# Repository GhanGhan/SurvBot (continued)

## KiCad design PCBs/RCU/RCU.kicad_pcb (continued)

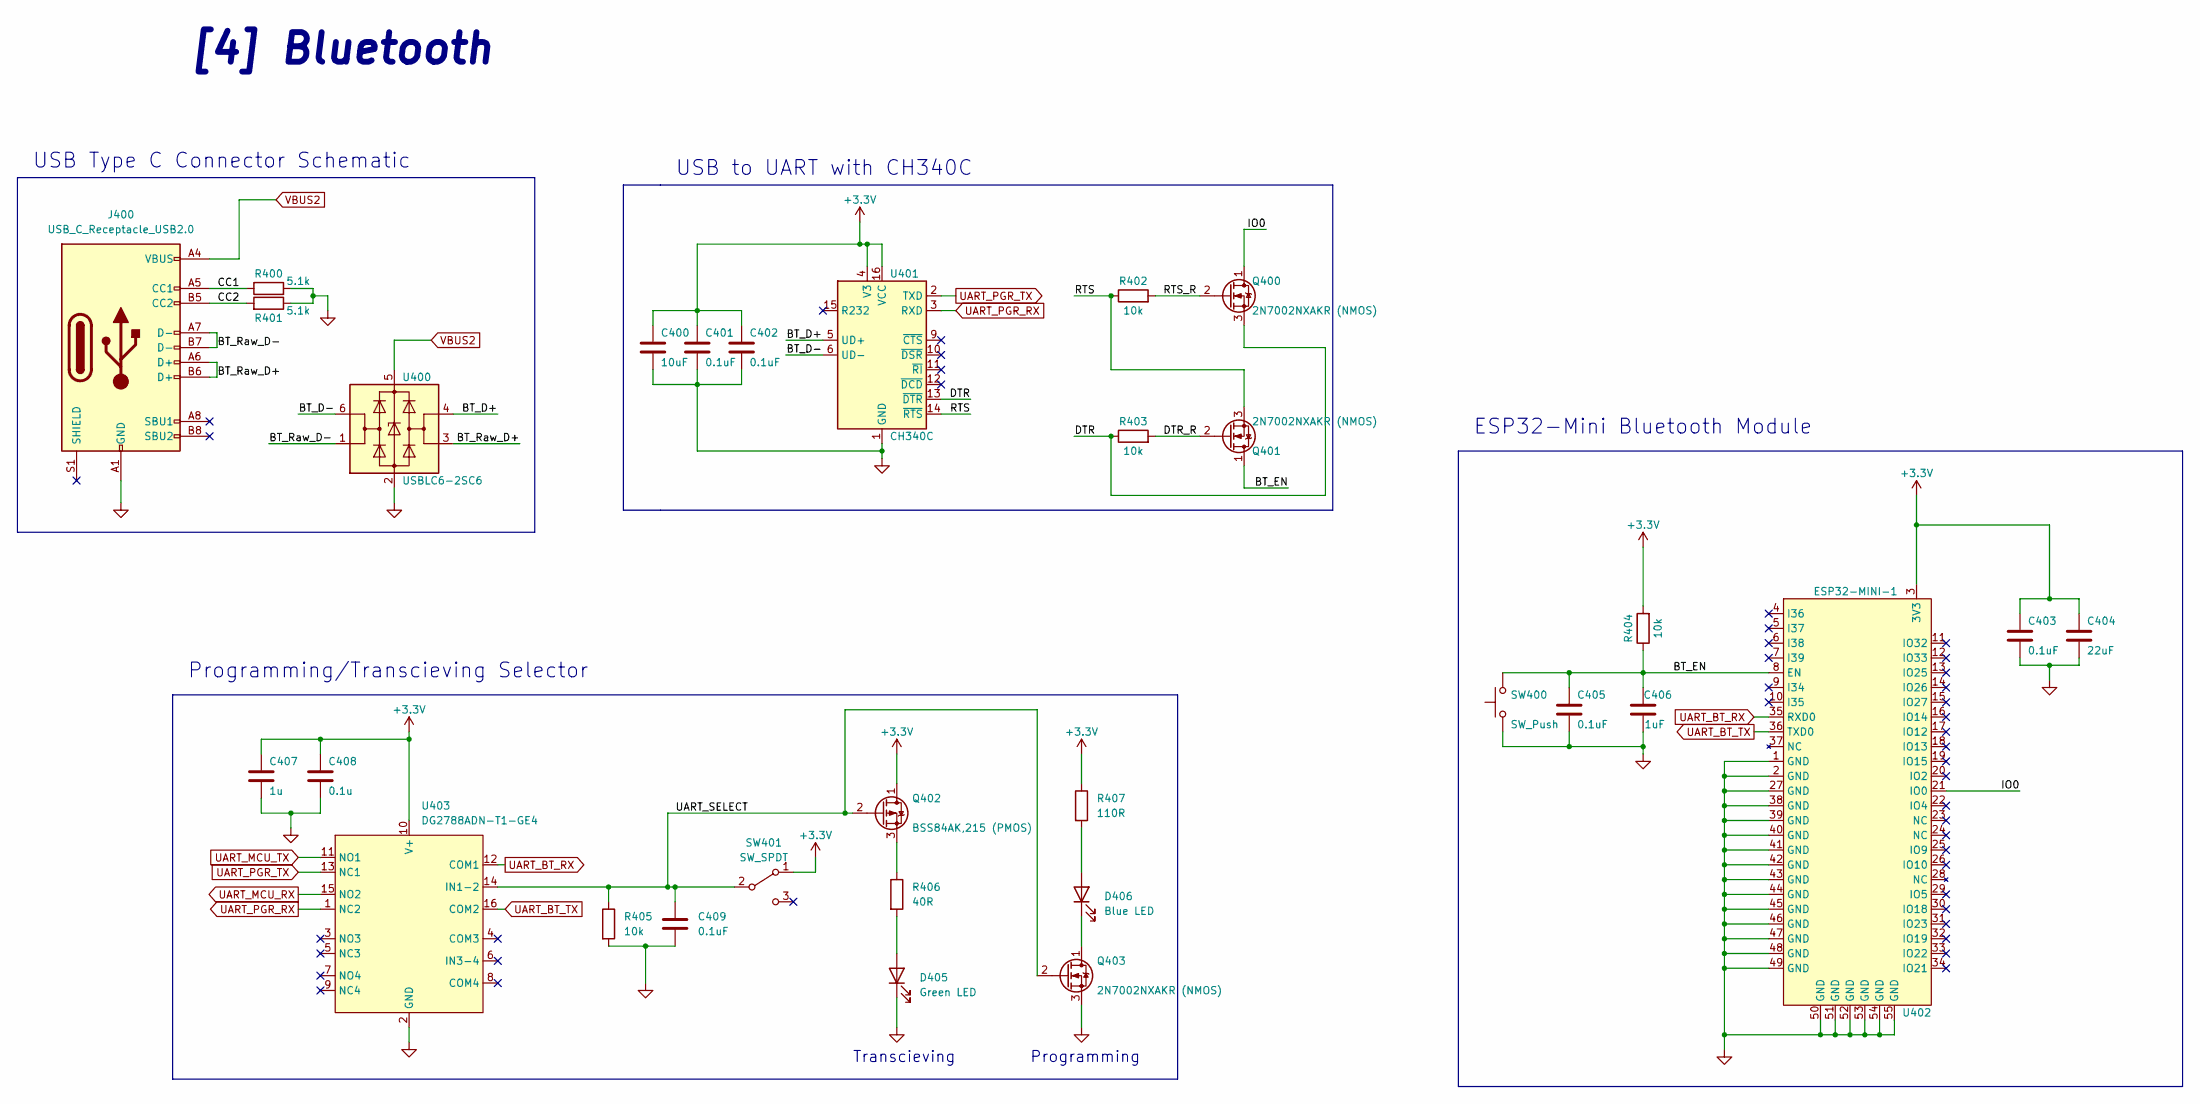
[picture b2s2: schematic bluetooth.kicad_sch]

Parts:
C400: 10uF; C_0603_1608Metric
C401, C402, C403, C405, C409: 0.1uF; C_0603_1608Metric
C404: 22uF; C_0603_1608Metric
C406: 1uF; C_0603_1608Metric
C407: 1u; C_0603_1608Metric
C408: 0.1u; C_0603_1608Metric
D405: Green LED; LED_0603_1608Metric
D406: Blue LED; LED_0603_1608Metric
J400: USB_C_Receptacle_USB2.0; USB_C_Receptacle_HRO_TYPE-C-31-M-12
Q400, Q401, Q403: 2N7002NXAKR (NMOS); SOT-23
Q402: BSS84AK,215 (PMOS); SOT-23
R400, R401: 5.1k; R_0603_1608Metric
R402, R403, R404, R405: 10k; R_0603_1608Metric
R406: 40R; R_0603_1608Metric
R407: 110R; R_0603_1608Metric
SW400: SW_Push; SW_SPST_B3U-1000P
SW401: SW_SPDT; SW_JS102011JCQN
U400: USBLC6-2SC6; SOT-23-6
U401: CH340C; SOP-16_3.9x9.9mm_P1.27mm
U402: ESP32-MINI-1; XCVR_ESP32-MINI-1-N4
U403: DG2788ADN-T1-GE4; QFN40P260X180X55-16N

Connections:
+3V3: C400.1, C401.1, C402.1, C403.1, C404.1, C407.1, C408.1, Q402.1 (D), R404.2, R407.1, SW401.1 (A), U401.4 (V3), U401.16 (VCC), U402.3 (3V3), U403.10 (V+); also elsewhere on the board
/[4] Bluetooth/BT_D+: U400.4 (I/O2), U401.5 (UD+)
/[4] Bluetooth/BT_D-: U400.6 (I/O1), U401.6 (UD-)
/[4] Bluetooth/BT_EN: C405.1, C406.1, Q401.1 (D), R404.1, SW400.2, U402.8 (EN)
/[4] Bluetooth/BT_Raw_D+: J400.A6 (D+), J400.B6 (D+), U400.3 (I/O2)
/[4] Bluetooth/BT_Raw_D-: J400.A7 (D-), J400.B7 (D-), U400.1 (I/O1)
/[4] Bluetooth/CC1: J400.A5 (CC1), R400.1
/[4] Bluetooth/CC2: J400.B5 (CC2), R401.2
/[4] Bluetooth/DTR: Q400.3 (S), R403.1, U401.13 (~DTR)
/[4] Bluetooth/DTR_R: Q401.2 (G), R403.2
/[4] Bluetooth/IO0: Q400.1 (D), U402.21 (IO0)
/[4] Bluetooth/RTS: Q401.3 (S), R402.1, U401.14 (~RTS)
/[4] Bluetooth/RTS_R: Q400.2 (G), R402.2
/[4] Bluetooth/UART_SELECT: C409.1, Q402.2 (G), Q403.2 (G), R405.1, SW401.2 (B), U403.14 (IN1-2)
unnamed: D405.2 (A), R406.2
unnamed: D406.1 (K), Q403.1 (D)
unnamed: D406.2 (A), R407.2
unnamed: Q402.3 (S), R406.1
UART_BT_RX: U402.35 (RXD0), U403.12 (COM1)
UART_BT_TX: U402.36 (TXD0), U403.16 (COM2)
UART_MCU_RX: U403.15 (NO2); also elsewhere on the board
UART_MCU_TX: U403.11 (NO1); also elsewhere on the board
UART_PGR_RX: U401.3 (RXD), U403.1 (NC2)
UART_PGR_TX: U401.2 (TXD), U403.13 (NC1)
VBUS2: J400.A4 (VBUS), J400.A9 (VBUS), J400.B4 (VBUS), J400.B9 (VBUS), U400.5 (VBUS); also elsewhere on the board

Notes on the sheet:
ESP32-Mini Bluetooth Module
[4] Bluetooth
Programming
USB Type C Connector Schematic
USB to UART with CH340C
Programming/Transcieving Selector
Transcieving

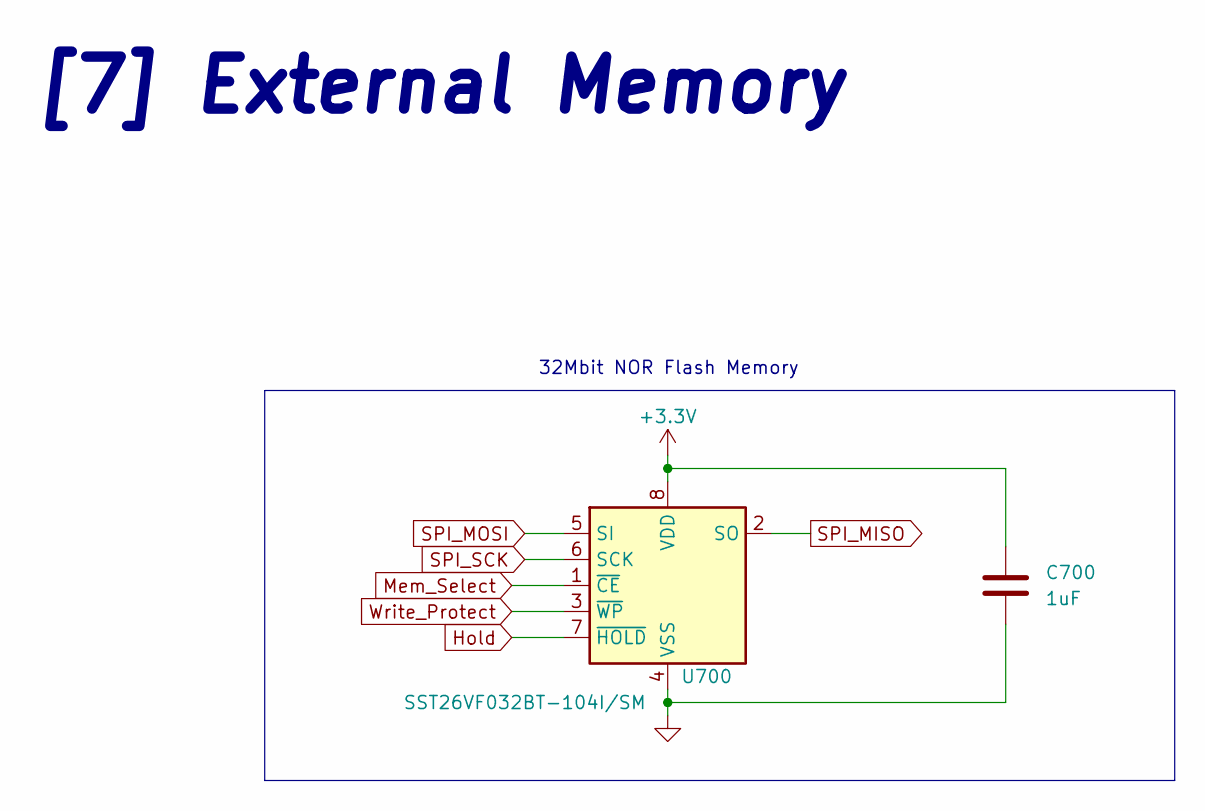
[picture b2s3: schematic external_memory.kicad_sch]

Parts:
C700: 1uF; C_0603_1608Metric
U700: SST26VF032BT-104I/SM; SOIC-8_5.275x5.275mm_P1.27mm

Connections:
+3V3: C700.2, U700.8 (VDD); also elsewhere on the board
Hold: U700.7 (~HOLD); also elsewhere on the board
Mem_Select: U700.1 (~CE); also elsewhere on the board
SPI_MISO: U700.2 (SO); also elsewhere on the board
SPI_MOSI: U700.5 (SI); also elsewhere on the board
SPI_SCK: U700.6 (SCK); also elsewhere on the board
Write_Protect: U700.3 (~WP); also elsewhere on the board

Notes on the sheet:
32Mbit NOR Flash Memory
[7] External Memory

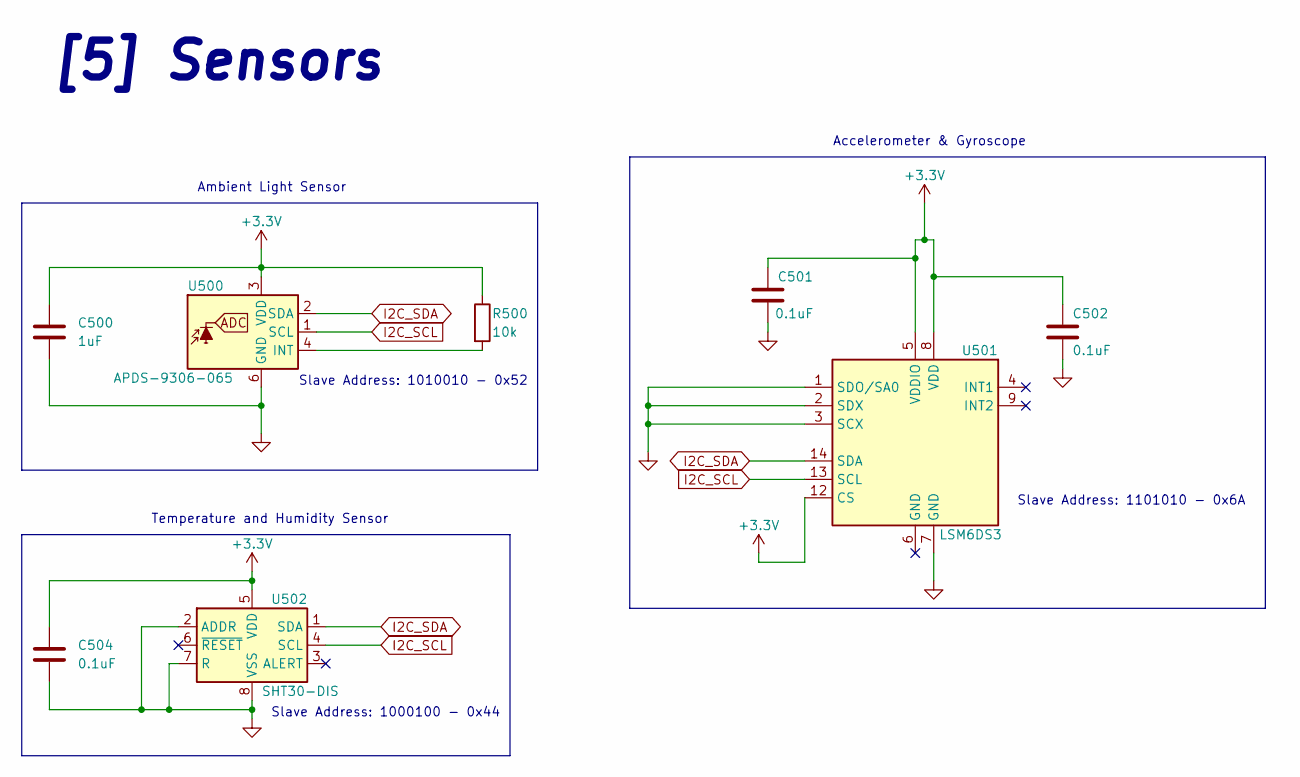
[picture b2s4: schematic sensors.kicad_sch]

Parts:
C500: 1uF; C_0603_1608Metric
C501, C502, C504: 0.1uF; C_0603_1608Metric
R500: 10k; R_0603_1608Metric
U500: APDS-9306-065; Broadcom_DFN-6_2x2mm_P0.65mm
U501: LSM6DS3; LGA-14_3x2.5mm_P0.5mm_LayoutBorder3x4y
U502: SHT30-DIS; Sensirion_DFN-8-1EP_2.5x2.5mm_P0.5mm_EP1.1x1.7mm

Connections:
+3V3: C500.1, C501.2, C502.2, C504.1, R500.1, U500.3 (VDD), U501.5 (VDDIO), U501.8 (VDD), U501.12 (CS), U502.5 (VDD); also elsewhere on the board
/[5] Sensors/Light_sensor INT_H: R500.2, U500.4 (INT)
I2C_SCL: U500.1 (SCL), U501.13 (SCL), U502.4 (SCL); also elsewhere on the board
I2C_SDA: U500.2 (SDA), U501.14 (SDA), U502.1 (SDA); also elsewhere on the board

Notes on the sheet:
Slave Address: 1101010 - 0x6A
Temperature and Humidity Sensor
[5] Sensors
Slave Address: 1000100 - 0x44
Accelerometer & Gyroscope
Ambient Light Sensor
Slave Address: 1010010 - 0x52

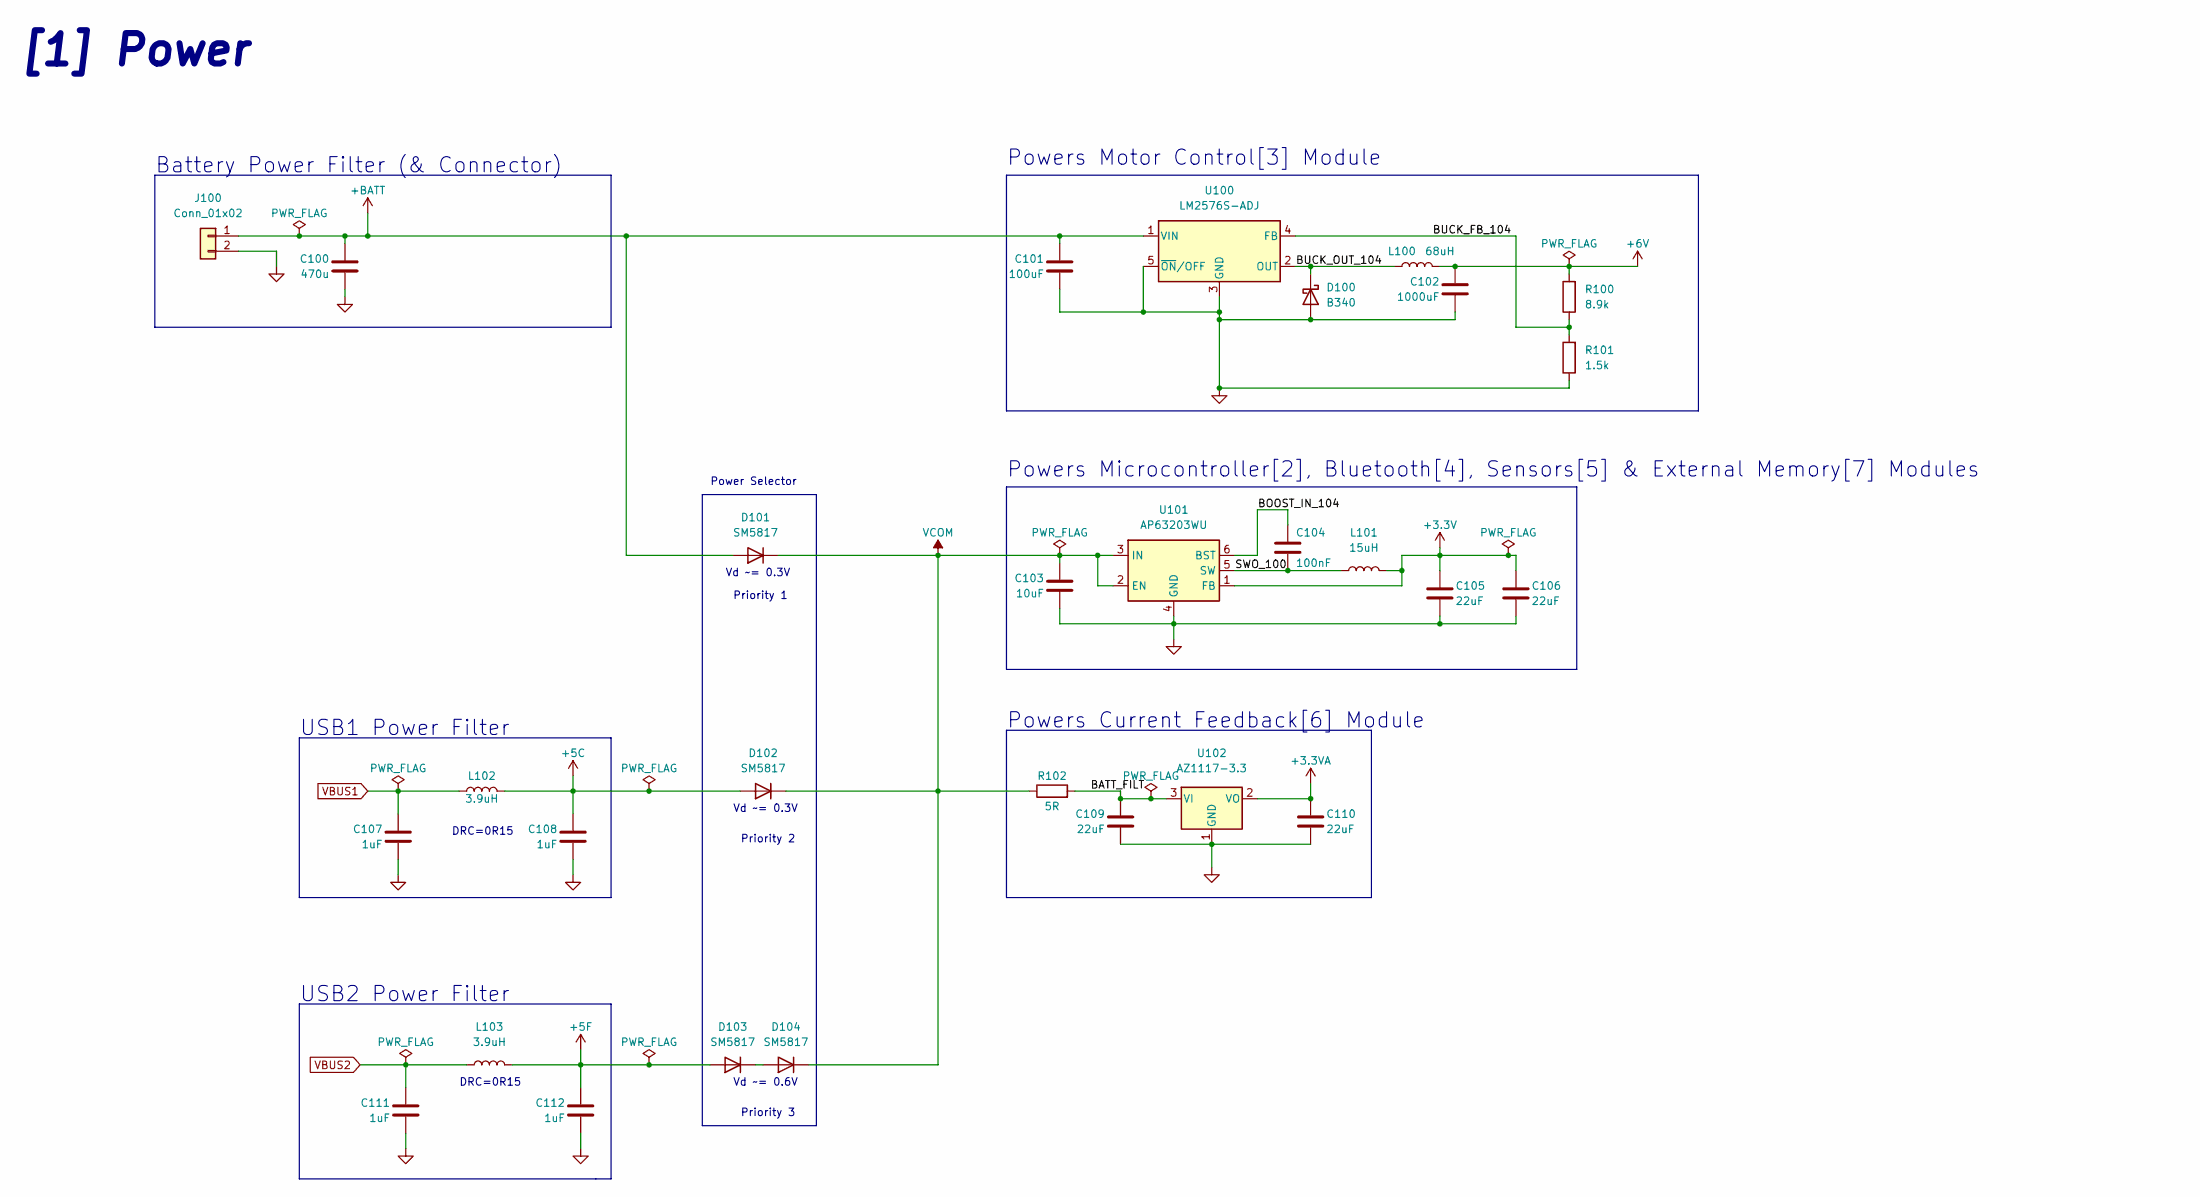
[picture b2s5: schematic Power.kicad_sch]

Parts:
C100: 470u; CP_Radial_D5.0mm_P2.50mm
C101: 100uF; CP_Radial_D5.0mm_P2.50mm
C102: 1000uF; CP_Radial_D5.0mm_P2.50mm
C103: 10uF; C_0603_1608Metric
C104: 100nF; C_0603_1608Metric
C105, C106, C109, C110: 22uF; C_0603_1608Metric
C107, C108, C111, C112: 1uF; C_0603_1608Metric
D100: B340; D_SMC
D101, D102, D103, D104: SM5817; SODFL3719X135N
J100: Conn_01x02; SolderWire-2sqmm_1x02_P7.8mm_D2mm_OD3.9mm
L100: 68uH; IND_MWSA1206S_SNL
L101: 15uH; L_0603_1608Metric
L102, L103: 3.9uH; L_0402_1005Metric
R100: 8.9k; R_0603_1608Metric
R101: 1.5k; R_0603_1608Metric
R102: 5R; R_0603_1608Metric
U100: LM2576S-ADJ; TO-263-5_TabPin3
U101: AP63203WU; TSOT-23-6
U102: AZ1117-3.3; TO-252-2

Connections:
+3.3VA: C110.1, U102.2 (VO); also elsewhere on the board
+3V3: C105.1, C106.1, L101.2, U101.1 (FB); also elsewhere on the board
+5C: C108.1, D102.2 (A), L102.2
+5F: C112.1, D103.2 (A), L103.2
+6V: C102.1, L100.2, R100.2; also elsewhere on the board
+BATT: C100.1, C101.1, D101.2 (A), J100.1, U100.1 (VIN)
/[1] Power/BATT_FILT: C109.1, R102.2, U102.3 (VI)
/[1] Power/BOOST_IN_104: C104.1, U101.6 (BST)
/[1] Power/BUCK_FB_104: R100.1, R101.2, U100.4 (FB)
/[1] Power/BUCK_OUT_104: D100.1 (K), L100.1, U100.2 (OUT)
/[1] Power/SWO_100: C104.2, L101.1, U101.5 (SW)
unnamed: D103.1 (K), D104.2 (A)
VBUS1: C107.1, L102.1; also elsewhere on the board
VBUS2: C111.1, L103.1; also elsewhere on the board
VCOM: C103.1, D101.1 (K), D102.1 (K), D104.1 (K), R102.1, U101.2 (EN), U101.3 (IN)

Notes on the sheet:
Battery Power Filter (& Connector)
Priority 3
Powers Microcontroller[2], Bluetooth[4], Sensors[5] & External Memory[7] Modules
Power Selector
Vd ~= 0.6V
Powers Current Feedback[6] Module
DRC=0R15
Vd ~= 0.3V
Powers Motor Control[3] Module
USB2 Power Filter
USB1 Power Filter
Priority 2
Priority 1
[1] Power

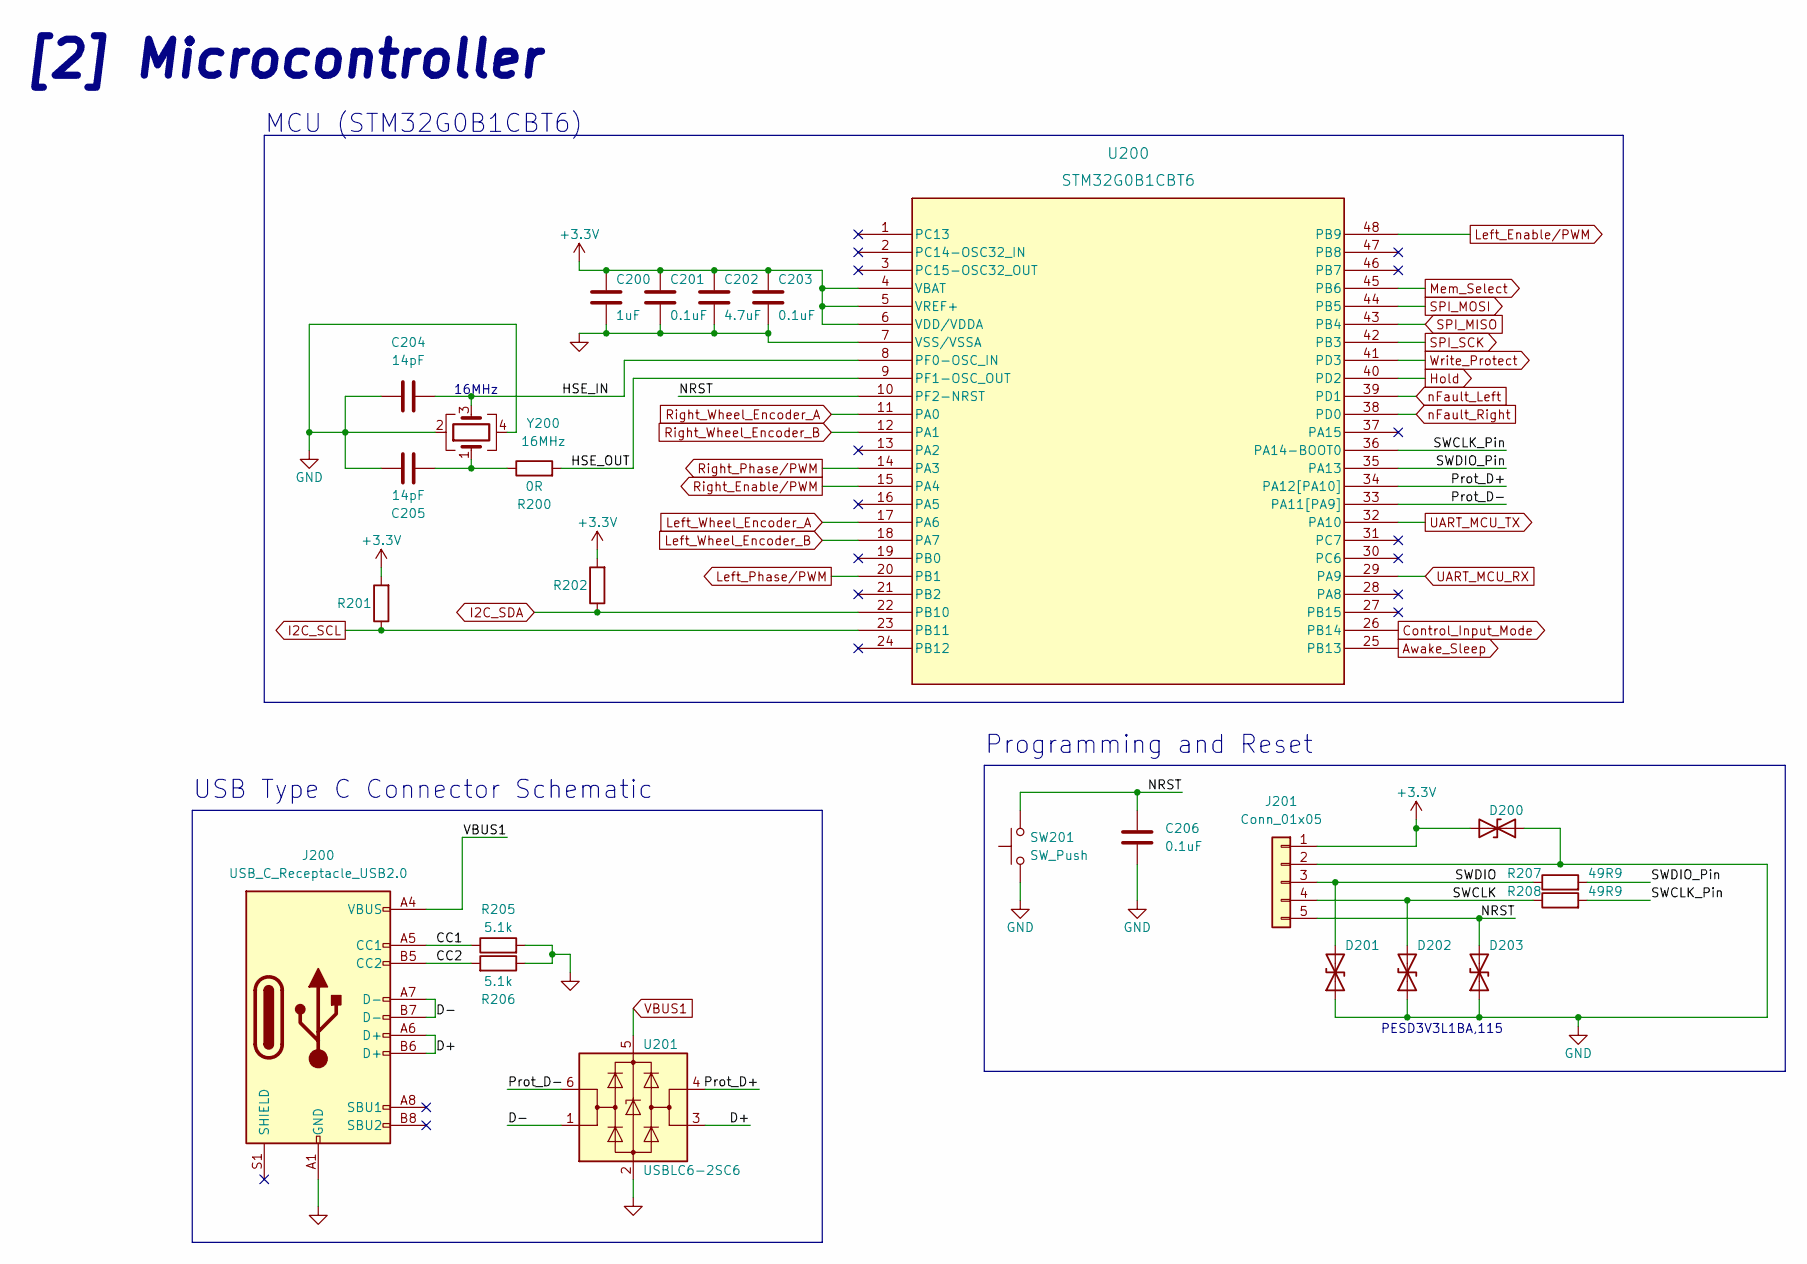
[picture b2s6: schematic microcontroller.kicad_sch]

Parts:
C200: 1uF; C_0402_1005Metric
C201, C203, C206: 0.1uF; C_0402_1005Metric
C202: 4.7uF; C_0402_1005Metric
C204, C205: 14pF; C_0402_1005Metric
D200, D201, D202, D203: PESD3V3L1BA,115; D_SOD-323
J200: USB_C_Receptacle_USB2.0; USB_C_Receptacle_HRO_TYPE-C-31-M-12
J201: Conn_01x05; PinHeader_1x05_P2.54mm_Vertical
R200: 0R; R_0402_1005Metric
R201, R202: (no value)
R205, R206: 5.1k; R_0603_1608Metric
R207, R208: 49R9; R_0603_1608Metric
SW201: SW_Push; SW_SPST_B3U-1000P
U200: STM32G0B1CBT6; LQFP-48_7x7mm_P0.5mm
U201: USBLC6-2SC6; SOT-23-6
Y200: 16MHz; Crystal_SMD_3225-4Pin_3.2x2.5mm

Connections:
+3V3: C200.1, C201.1, C202.1, C203.1, D200.2 (A2), J201.1, R201.2, R202.2, U200.4 (VBAT), U200.5 (VREF+), U200.6 (VDD/VDDA); also elsewhere on the board
/[2] Microcontroller/CC1: J200.A5 (CC1), R205.1
/[2] Microcontroller/CC2: J200.B5 (CC2), R206.2
/[2] Microcontroller/D+: J200.A6 (D+), J200.B6 (D+), U201.3 (I/O2)
/[2] Microcontroller/D-: J200.A7 (D-), J200.B7 (D-), U201.1 (I/O1)
/[2] Microcontroller/HSE_IN: C204.1, U200.8 (PF0-OSC_IN), Y200.3
/[2] Microcontroller/HSE_OUT: R200.2, U200.9 (PF1-OSC_OUT)
/[2] Microcontroller/NRST: C206.1, D203.2 (A2), J201.5, SW201.2, U200.10 (PF2-NRST)
/[2] Microcontroller/Prot_D+: U200.34 (PA12[PA10]), U201.4 (I/O2)
/[2] Microcontroller/Prot_D-: U200.33 (PA11[PA9]), U201.6 (I/O1)
/[2] Microcontroller/SWCLK: D202.2 (A2), J201.4, R208.1
/[2] Microcontroller/SWCLK_Pin: R208.2, U200.36 (PA14-BOOT0)
/[2] Microcontroller/SWDIO: D201.2 (A2), J201.3, R207.1
/[2] Microcontroller/SWDIO_Pin: R207.2, U200.35 (PA13)
Awake_Sleep: U200.25 (PB13); also elsewhere on the board
Control_Input_Mode: U200.26 (PB14); also elsewhere on the board
Hold: U200.40 (PD2); also elsewhere on the board
I2C_SCL: R201.1, U200.23 (PB11); also elsewhere on the board
I2C_SDA: R202.1, U200.22 (PB10); also elsewhere on the board
Left_Enable/PWM: U200.48 (PB9); also elsewhere on the board
Left_Phase/PWM: U200.20 (PB1); also elsewhere on the board
Left_Wheel_Encoder_A: U200.17 (PA6); also elsewhere on the board
Left_Wheel_Encoder_B: U200.18 (PA7); also elsewhere on the board
Mem_Select: U200.45 (PB6); also elsewhere on the board
unnamed: C205.2, R200.1, Y200.1
Right_Enable/PWM: U200.15 (PA4); also elsewhere on the board
Right_Phase/PWM: U200.14 (PA3); also elsewhere on the board
Right_Wheel_Encoder_A: U200.11 (PA0); also elsewhere on the board
Right_Wheel_Encoder_B: U200.12 (PA1); also elsewhere on the board
SPI_MISO: U200.43 (PB4); also elsewhere on the board
SPI_MOSI: U200.44 (PB5); also elsewhere on the board
SPI_SCK: U200.42 (PB3); also elsewhere on the board
UART_MCU_RX: U200.29 (PA9); also elsewhere on the board
UART_MCU_TX: U200.32 (PA10); also elsewhere on the board
VBUS1: J200.A4 (VBUS), J200.A9 (VBUS), J200.B4 (VBUS), J200.B9 (VBUS), U201.5 (VBUS); also elsewhere on the board
Write_Protect: U200.41 (PD3); also elsewhere on the board
nFault_Left: U200.39 (PD1); also elsewhere on the board
nFault_Right: U200.38 (PD0); also elsewhere on the board

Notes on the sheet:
Programming and Reset
[2] Microcontroller
MCU (STM32G0B1CBT6)
PESD3V3L1BA,115
16MHz
USB Type C Connector Schematic

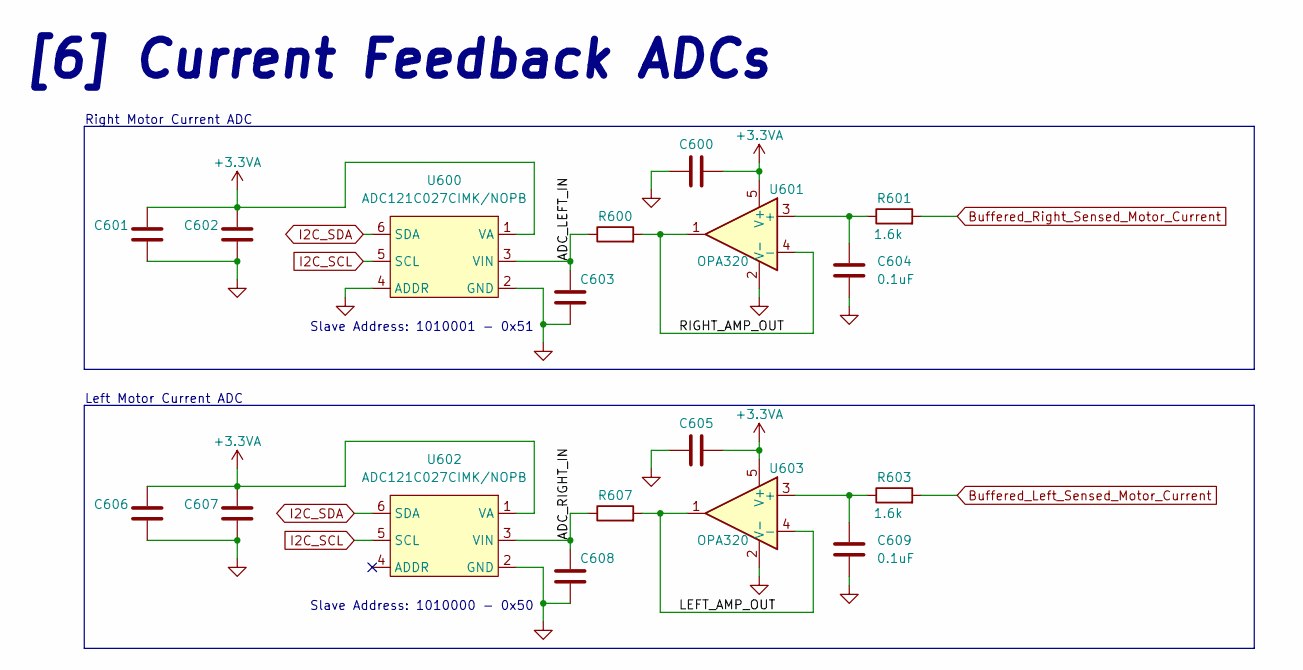
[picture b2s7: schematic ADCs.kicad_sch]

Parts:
C600, C601, C602, C603, C605, C606, C607, C608: (no value)
C604, C609: 0.1uF; C_0603_1608Metric
R600, R607: (no value)
R601, R603: 1.6k; R_0603_1608Metric
U600, U602: ADC121C027CIMK/NOPB; TSOT-23-6
U601, U603: OPA320; SOT-23-5

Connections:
+3.3VA: C600.2, C601.1, C602.1, C605.2, C606.1, C607.1, U600.1 (VA), U601.5 (V+), U602.1 (VA), U603.5 (V+); also elsewhere on the board
/[6] ADCs/ADC_LEFT_IN: C603.1, R600.1, U600.3 (VIN)
/[6] ADCs/ADC_RIGHT_IN: C608.1, R607.1, U602.3 (VIN)
/[6] ADCs/LEFT_AMP_OUT: R607.2, U603.1, U603.4 (-)
/[6] ADCs/RIGHT_AMP_OUT: R600.2, U601.1, U601.4 (-)
Buffered_Left_Sensed_Motor_Current: R603.2; also elsewhere on the board
Buffered_Right_Sensed_Motor_Current: R601.2; also elsewhere on the board
I2C_SCL: U600.5 (SCL), U602.5 (SCL); also elsewhere on the board
I2C_SDA: U600.6 (SDA), U602.6 (SDA); also elsewhere on the board
unnamed: C604.2, R601.1, U601.3 (+)
unnamed: C609.2, R603.1, U603.3 (+)

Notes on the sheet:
Right Motor Current ADC
Left Motor Current ADC
Slave Address: 1010001 - 0x51
[6] Current Feedback ADCs
Slave Address: 1010000 - 0x50

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
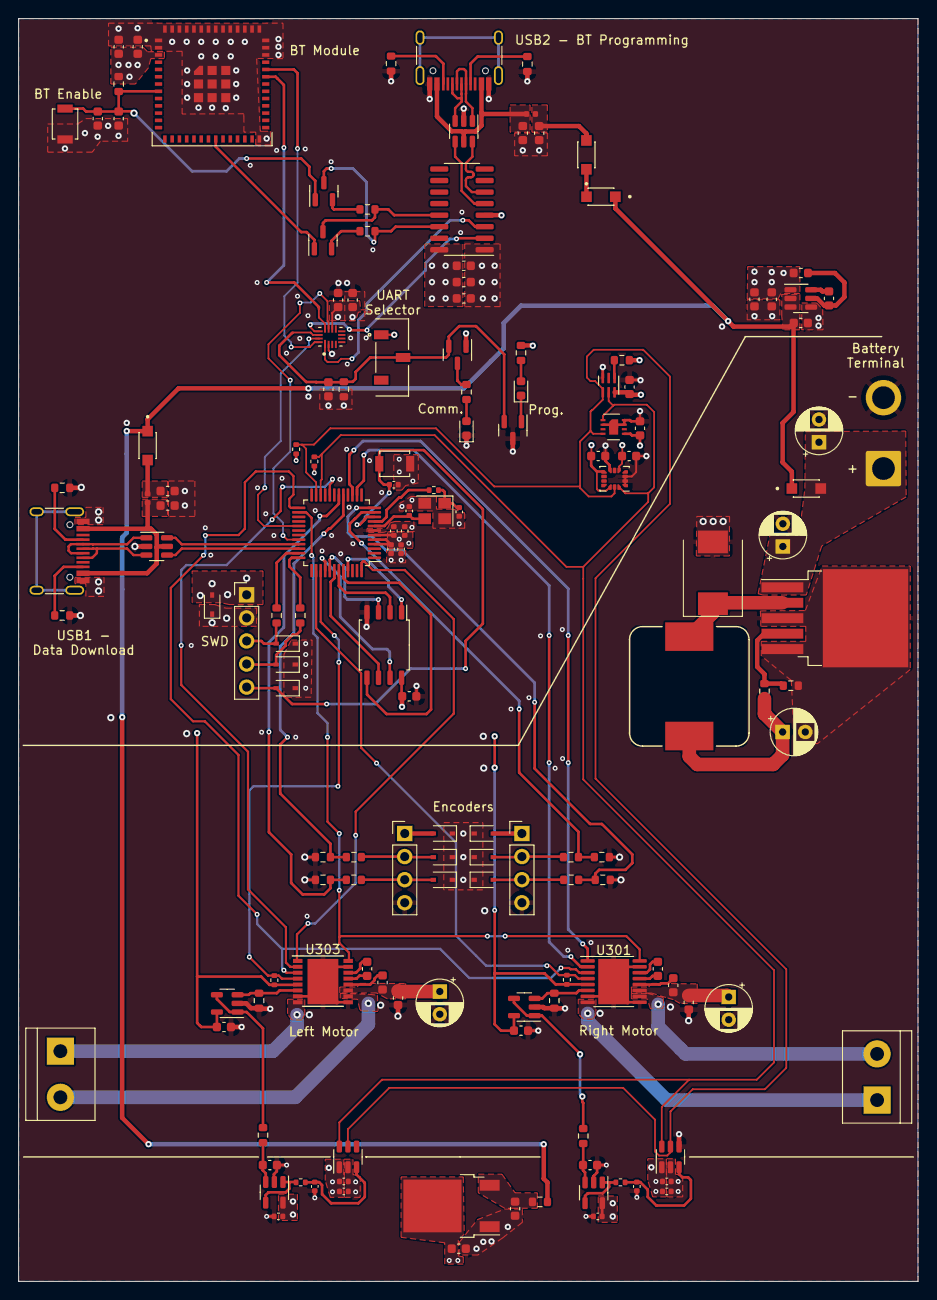
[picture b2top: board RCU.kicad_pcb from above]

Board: 4 copper layers, 99.0 x 139.0 mm, 148 parts (0 on the bottom side), 98 nets.

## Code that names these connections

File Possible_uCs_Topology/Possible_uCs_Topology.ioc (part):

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Mcu.Name=STM32G0B1C(B-C-E)Tx
Mcu.Package=LQFP48
Mcu.UserName=STM32G0B1CBTx
PA0.GPIOParameters=GPIO_Label
PA0.GPIO_Label=Right_Wheel_Encoder_A
PA0.Signal=S_TIM2_CH1_ETR
PA1.GPIOParameters=GPIO_Label
PA1.GPIO_Label=Right_Wheel_Encoder_B
PA1.Signal=S_TIM2_CH2
PA10.Mode=Asynchronous
PA10.Signal=USART1_RX
PA11\ [PA9].Mode=Device
PA11\ [PA9].Signal=USB_DM
PA12\ [PA10].Mode=Device
PA12\ [PA10].Signal=USB_DP
PA13.Mode=Serial_Wire
PA13.Signal=SYS_SWDIO
PA14-BOOT0.Mode=Serial_Wire
PA14-BOOT0.Signal=SYS_SWCLK
PA3.GPIOParameters=GPIO_Label
PA3.GPIO_Label=Right_Phase/PWM
PA3.Signal=S_TIM2_CH4
PA4.GPIOParameters=GPIO_Label
PA4.GPIO_Label=Right_Enable/PWM
PA4.Signal=S_TIM14_CH1
PA6.GPIOParameters=GPIO_Label
PA6.GPIO_Label=Left_Wheel_Encoder_A
PA6.Signal=S_TIM3_CH1
PA7.GPIOParameters=GPIO_Label
PA7.GPIO_Label=Right_Wheel_Encoder_B
PA7.Signal=S_TIM3_CH2
PA9.Mode=Asynchronous
PA9.Signal=USART1_TX
PB1.GPIOParameters=GPIO_Label
PB1.GPIO_Label=Left_Phase/PWM
PB1.Signal=S_TIM3_CH4
PB10.Mode=I2C
PB10.Signal=I2C2_SCL
PB11.Mode=I2C
PB11.Signal=I2C2_SDA
PB13.GPIOParameters=GPIO_Label
PB13.GPIO_Label=Awake_Sleep
PB13.Signal=GPIO_Output
PB14.GPIOParameters=GPIO_Label
PB14.GPIO_Label=Control_Input_Mode
PB14.Signal=GPIO_Output
PB3.Mode=Full_Duplex_Master
PB3.Signal=SPI3_SCK
PB4.Mode=Full_Duplex_Master
PB4.Signal=SPI3_MISO
PB5.Mode=Full_Duplex_Master
PB5.Signal=SPI3_MOSI
PB9.GPIOParameters=GPIO_Label
PB9.GPIO_Label=Left_Enable/PWM
PB9.Signal=S_TIM4_CH4
PD0.GPIOParameters=GPIO_Label
PD0.GPIO_Label=nFault_Right
PD0.Signal=GPIO_Input
PD1.GPIOParameters=GPIO_Label
PD1.GPIO_Label=nFault_Left
PD1.Signal=GPIO_Input
PF0-OSC_IN\ (PF0).Mode=HSE-External-Oscillator
PF0-OSC_IN\ (PF0).Signal=RCC_OSC_IN
PF1-OSC_OUT\ (PF1).Mode=HSE-External-Oscillator
PF1-OSC_OUT\ (PF1).Signal=RCC_OSC_OUT
RCC.HSE_VALUE=8000000
RCC.SYSCLKFreq_VALUE=16000000
board=custom

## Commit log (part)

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2024-03-25 Bought materials needed for prototyping, chassis, motor, motor controllers, environment sensors
2024-03-28 Add 'Testing' folder for where I will prototype formware to interact with Sensors and control motors, directional motor speed control successful
2024-04-01 Add comments about forward and reverse rotation
2024-04-02 Configuration for communcating over UART
2024-04-05 Read values from one quadrature encoder every 10 millseconds (period set by TIM2) and outputs motor speed
2024-04-07 Deleted unrelated projects from workspace
2024-04-07 Successful UART transmit test, words and digits
2024-04-07 Can send speed commands to UART and correctly parse them
2024-04-08 Add parsing.c and parsing.h file, holds function to aqcuire velocity speed command from UART
2024-04-08 Removed unused code
2024-04-13 Changed HAL_TIM_ENCODER_Start_IT to HAL_TIM_ENCODER_Start, not using external encoder interrupt
2024-04-13 Get PWM command from UART, motor rotates as directed, need to change channel/direction association
2024-04-14 Add PID header and source file
2024-04-14 Changed if statement in HAL_UART_Recieve_IT so that positve speed commands correspond with positive rotation and vice-versa
2024-04-17 Corrected PID equation, add more information in MSG2, and corrected issue that caused motor to rotate at max speed at times
    Integral part of equation has to be multiplied by the time period, and in HAL_TIM_PeriodEleapsedCallback, the if statements that decide whether to try to rotate the wheel in the forward or reverse di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
2024-04-17 Cleaned up and commented HAL_TIM_PeriodElapsedCallback
2024-04-17 Rename variables velocity and speed to velocity_command and wheel_speed, display velocity_command instead of controller.setpoint
2024-04-19 Started Robot PCB schematic - RCU (Robot Control Unit
    Using STM32G0B1CBTC, imported the uC's design files (footprint, symbol and 3d file)
2024-04-19 Added PWM pins and UART pins
2024-06-02 Mapped out Motor Control, I2C, UART and USB pins on microcontroller, will be using STM32G0B1CBT6
2024-06-02 Updated microcontroller schematic and created motor_control schematic
    Changed all the net lables to global lavels except for NRST and USB_, added crystal resonator circuit, created DRV8876 symbol and added control signals to it
2024-06-04 Add Awake_Sleep and Contro_Input_Mode pin assignments to uC
2024-06-09 Decided on Temperature_Humidity and Ambient Light Sensors
2024-06-17 Added Accelerometer_Gyroscope IC with supplementary components
2024-06-17 Added ADC that will convert sensed motor currents to I2C
2024-06-17 Prepended 'SDA' and 'SCL' global labels with 'I2C_'
2024-06-18 Added ADC circuit for sensing motor currents
2024-06-18 Decreased paper size for motor control schematic and corrected the name of op amp used in ADC
2024-06-28 Add output buffer to IPROPI pin of Motor Driver ICs and low pass RC filter and input buffer to ADCs
2024-06-28 Added Bluetooth module ESP32-MINI-1
2024-07-02 Adding programming capability and starting power selector circuit
2024-07-02 Update README.md
    Add project overview
2024-07-16 Start drafting power module
2024-07-16 Finished Power module with power selector
2024-07-22 Completed UART multiplexer circuit
2024-07-22 Complete ESP32 programming circuit
2024-07-25 Finished Microcontroller schematic
2024-07-25 Microcontroller will take nFaults of both motor controllers as inputs
2024-07-26 Add USB power filter circuitry and corrected Motor Driver schematic
2024-07-26 Add battery filter circuit, corrected cap values for 3.3V regulators, used different output power floag for Bottom regulator so that it only powers the Bluetooth susbsystem
2024-07-26 Numbered and ordered all of the modules
2024-07-26 Annotated all of the components in Power
2024-07-26 Annotated all components in motor control
2024-07-26 Annotated all components in Bluetooth
2024-07-26 Annotated all components in ADC schematic
2024-07-26 Label power sub-circuits
2024-07-26 Finished labelling all of microcontroller schematic
2024-07-26 Sectioned ADC module and corrected Motor current output name
2024-07-26 Update README.md
    Corrected Block Diagram
2024-07-26 Update README.md
    Added schematic diagrams
2024-07-27 The shared SWCLK/BOOT0 pin has an internal pull-down resistor, and in the case where SWCLK is shared and are programming with SWD, just need NRST conncted to the STLink-V2 module
2024-07-28 Added 16Mhz crystal oscillator, along with load capacitors and external resistor
2024-07-29 Will use a 6V battery instead of 9V, since motor I am using is rated for 6V
2024-07-30 Updated switching regulator inductor values and annotated 4th diode in power schematic
2024-07-31 Use Rext = 0 ohms for oscillator circuit
2024-08-01 Corrected cap values in regulators, changed voltage after battery filter to 9V, will use a 6V regulator to power motors in the near future
2024-08-02 Corrected C302 and C305 values in motor drive units, should be 22nF, not 22uF
2024-08-02 Add reference designators to adjustable regulator circuit
2024-08-02 Replaced ADCs with ADC121C027, easy to program the addresses
2024-08-04 Add filtering capacitors to microcontroller circuit
2024-08-04 scaled down encoder output from 6V to 4V
2024-08-05 Added ESD protection to 3.3V pin of SWD connector, and made motor sheet larger
2024-08-05 Add add bidirectional ESD/TVS diodes to encoder and motor terminals
2024-08-10 Corrected resistor values for stepping down encoder output voltage
2024-08-10 Add 200uF bulk capacitor to motor control drivers
2024-08-10 Add decoupling capacitors to CH340C IC in Bluetooth module
2024-08-10 Corrected ESP32-Mini bypass caps and added push-button reset circuit
2024-08-10 Added bypass capacitors to IC switch, the datasheet did not recomend any
2024-08-10 Add bypass caps to omp amps in sensors module
2024-08-10 Updated ADC schematic to match application note in ADC and op-amp data sheets
2024-08-10 Reordered pin 5 and 6 for 3.3V regulators, and labeled nets
2024-08-10 Fully annotate power schematic
2024-08-10 Labeled all caps and resistors
2024-08-11 labeled all nets in motor_control schematic
2024-08-11 rotated 3.3V of CS pin of IMU in sensors schematic
2024-08-11 Fully annotated ADC schematic
2024-08-11 Removed TVS diodes for motor terminals, label TVS diodes for encoder, using OPA320 op amps in motor control schematic, it is now fully annotated
2024-08-11 Schematic cleanup
2024-08-11 Update README.md
    Updated schematic images
2024-08-11 Wrote that first regulator in power schematic also powers the external memory
2024-08-11 Changed sheet numbering
2024-08-12 Corrected SPI_MOSI and SPI_MISO labels on U700 - external memory
2024-08-12 Wrote slave address for all I2C ICs in binary and hex
2024-08-16 Changed UART selector led resistor values, and assigned colours
2024-08-17 Add OPA320, DRV8876, Motor Terminal and encoder footprints
2024-08-19 Add footprint to rest of IC's except ESP32
2024-08-19 Add footprint to power module diodes, and replaced 1N4148W with 2 SM5817's
2024-08-19 Add soler wire connections for battery power
2024-08-20 Changed Programming/Transcieving button to a slide switch
2024-08-20 Add footprints to leds, fets and push buttons
2024-08-20 Add footrpints to TVS diodes in [3]
2024-08-20 Got ESP32-MINI footprint
2024-08-20 Passed ERC
2024-08-20 Changed 55_1 ...55_9 pads to all 55
2024-08-20 Corrected footprint for U200
2024-08-20 Roughly sectioned modules
2024-08-20 Added stackup - JLC7628
2024-08-21 Changed filter caps for uC to 0402s
2024-08-21 Finished mcu placement
2024-08-22 Added 3d models and board outline on edge cuts layer
2024-08-22 Added motor driver footrpint and replaced diode 1N5822 with B340AE-13
2024-08-22 Course layout complete, added all 3d models
2024-08-22 organized analog section
2024-08-22 More rearangment, added 3d model to light and temp/humidity sensor
2024-08-22 Performed ground pour on internal ground layer
2024-08-22 Added split 3.3V and 6V VCC plane
2024-08-22 traced USB circuitry
2024-08-23 changed pad clearance of uart selector to 0.1mm
2024-08-23 Completed tracing Bluetooth module
2024-08-23 Update README.md
    Updated Schematic Diagrams
2024-08-27 laid and routed Current feedback
2024-08-27 Routed external memory
2024-08-27 routed 6V regulator
2024-08-27 Finished routing and change signals layers to mixed
2024-08-27 Changed priority of non-ground copper pours to 1
2024-08-27 Changed priority level of Left/Right_Out_2 to 2
2024-08-27 Added grouding vias for signal vias
2024-08-27 Added Silkscreen labels
2024-08-28 Finished adding grounding vias and Ran DRC
2024-09-04 Update README.md
    Provided descriptions of schematic
2024-09-04 Update README.md
    Added 3d View of PCB
2024-09-08 Corrected R100 value, it is now 5.9k instead of 8.9k
2024-09-09 Added Self-made Altium libraries made for the SurvBot project
2024-09-10 Updated Schematic and Footprint libraries
2024-09-10 Add Altium Designer project for SurvBot RCU
2024-09-10 Added DRV8876 symbol and footprint
2024-09-10 Added opamp-opa320 symbol and footprint
2024-09-10 Corrected power rating of 5R1 resistor
2024-09-10 Added USB Type C connector to Bluetooth schematic
2024-09-11 Add CH340C - USB Converter
2024-09-11 Complete USB to UART and Program/Transieve selector circuits
2024-09-11 Add ESP32-C3-MINI-1-N4 module schematic and footprint
2024-09-12 Complete Sensors Schematic
2024-09-12 Corrected op amp symbol
2024-09-12 Finish CurrentFeedback Schematic
2024-09-12 Labelled all nets
2024-09-12 Took care of valid DRC errors and warnings
2024-09-12 Added schematics to project overview
2024-09-12 Add Block to all schematics
2024-09-14 Add stackup and impedance trace
2024-09-14 Corrected ESP32-Mini footprint pin assignment
2024-09-14 Corrected TVS diode footprint pin assignment
2024-09-14 Finished rough module layout
2024-09-16 Corrected analog IC power pins and change BATT_FILT to VCOM_FILT
2024-09-16 Add power net class
2024-09-16 Add signal net class
2024-09-16 Added Power and Signal trace rules
2024-09-16 Add routing via rule
2024-09-16 Routed MCU
2024-09-16 Add High-Speed Length match rules, match lengths of BT_PROT_USB
2024-09-17 Routed Bluetooth
2024-09-17 Rout Externam Memory
2024-09-17 Routed motor Drivers
2024-09-17 Added split power plane
2024-09-17 Assigned vias in Motor Driver thermal pads to ground
2024-09-17 Add stitching vias
2024-09-17 Add more stitching vias
2024-09-17 Started adding silkscreen text
2024-09-18 Updated rules, electrical issues appear to be solved, still have solder mask and silk issues, but they are low priority for now
2024-09-18 Add BOM
2024-09-18 Exported BOM
2024-09-18 Add revision numbers
2024-09-18 Added supply nets rules
2024-10-03 Start SurvBot Remote Controller
2024-12-23 Add 3.3V Output buck converter to Survbot controller power schematic
2024-12-26 Add battery and USB as power sources
2024-12-28 Added ESP32-C3-MINI-1 to remote controller
2025-01-12 Add USB_C connector and USB_UART programmer to remote controller
2025-02-09 Decided on microcontroller ESP32-WROOM-32E(-N4)
2025-02-09 Update programming circuit for remote controller
2025-02-12 Add power multiplexing for 9V battery and USB power
2025-02-12 Finish power schematic, 3.3V buck converter and 3V LDO
2025-02-12 Add Power on indicator light, made small corrections
2025-02-12 Add power switch
2025-02-17 Added Thumb joystick symbols, and finish UI schematic with joysticks to control rotational and linear velocity
2025-02-17 Labeled all nets, corrected some labels, added battery-cell symbol
2025-02-20 Annotate components
2025-02-20 Add footprints except connectors, buttons and switches
2025-02-22 Add USB receptacle and LCD footprints
2025-02-22 Add Joystick footprint and passed ERC
2025-02-24 Updated joystick symbol, correct Dual fet footprint and annotated news in power toggle circuit
2025-03-05 Add board rules and stack up
2025-03-05 Finish rough layout, add 3D model of ESP32, pushbuttons, Display, tactile switch
2025-03-06 Added power button and battery (holder) 3D models
2025-03-16 Added new symbol fields and completed BOM
2025-03-17 Laid out components and PCB shape
2025-03-17 Completed more routing and copper pours
2025-03-17 Add grounding and stitching vias
2025-03-17 Added differential USB signal
